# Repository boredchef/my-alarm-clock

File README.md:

# my alarm clock 
this is an alarm clock using a pcb with an esp32, buzzer and display. the alarm clock also has an enclosure designed in Onshape. to control the alarm clock there are 4 keyswitches and a rotary encoder knob. 

## challenges
for this project, the firmware needed a lot of different variables in order to function like the current time and the alarm time, the pins for the buttons and the different states for buttons, the overall clock and substate fields like setting hours/minutes while setting time. this project really helped me understand how to manage all these by defining functions for checking buttons or checking the time. 

## current features
* set time/alarm
* rotary encoder knob
* loud buzzer when alarm rings

## planned firmware features
* using display instead of serial monitor
* snooze alarm function

## BoM
| components | why/what | 
| ------ | ------ |
| esp32 c3 | microcontroller |
| MX-style keyboard switches | alarm controls | 
| 2.25 in TFT screen | display |
| 3.3v piezo buzzer | beep beep beep |
| 8 pin male header | for more pins |  
| jumper wire | connect display to headers |
| M3x8mm screws | connect case together | 
| rotary encoder knob | set hours/minutes | 

## more pictures
| alarm case | exploded view | back of pcb | front of pcb | pcb design | schematic | 
| ---- | ---- | ---- | ---- | ---- | ---- |
|  |  |  |  |  |  |

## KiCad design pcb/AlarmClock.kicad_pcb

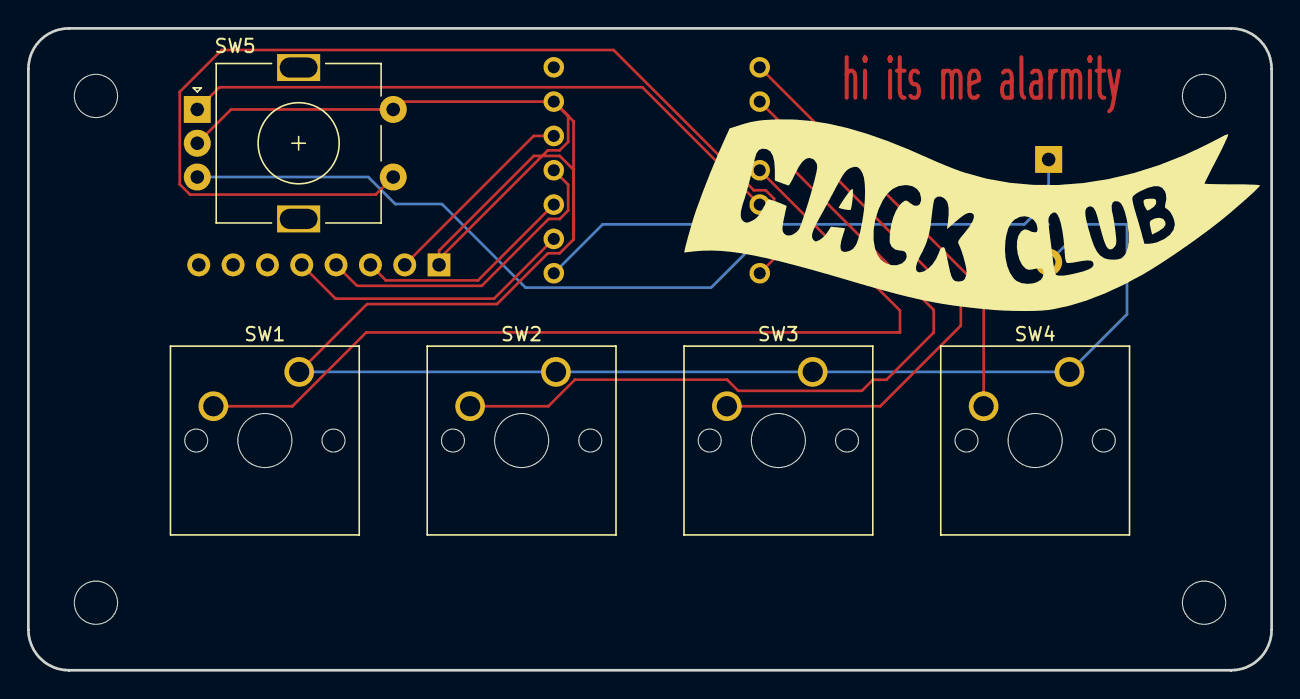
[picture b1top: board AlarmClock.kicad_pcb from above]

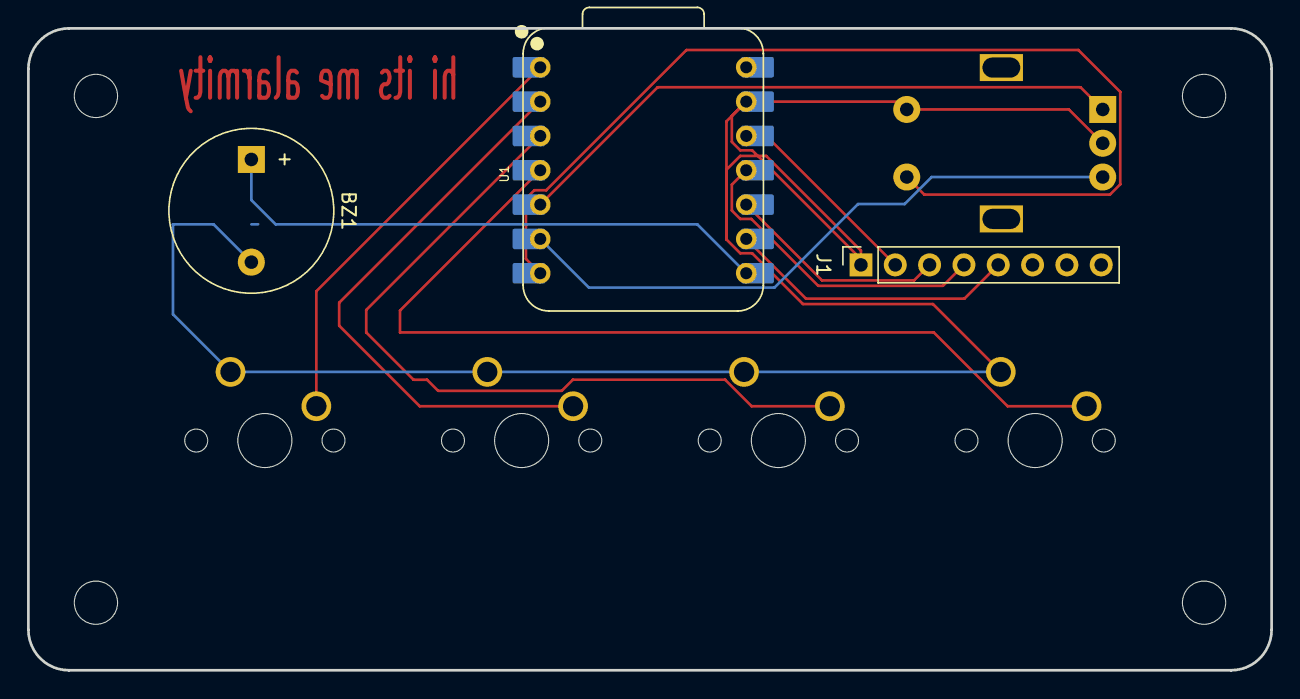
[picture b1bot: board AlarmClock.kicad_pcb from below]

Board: 2 copper layers, 92.0 x 47.5 mm, 12 parts (3 on the bottom side), 13 nets.

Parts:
BZ1: Buzzer; Buzzer_12x9.5RM7.6
H1, H2, H3, H4: MountingHole; MountingHole_3.2mm_M3
J1: Conn_01x08_Pin; PinSocket_1x08_P2.54mm_Vertical
SW1, SW2, SW3, SW4: SW_Push; SW_Cherry_MX_1.00u_PCB
SW5: RotaryEncoder_Switch; RotaryEncoder_Alps_EC11E-Switch_Vertical_H20mm
U1: XIAO-ESP32-C3-SMD; XIAO-ESP32-C3-DIP

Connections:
+3.3V: J1.2, U1.12 (3V3_OUT)
/A: SW5.A, U1.5 (D4)
/B: SW5.B, U1.6 (D5)
/RST: J1.5, U1.9 (D8)
/SCL: J1.3, U1.10 (D9/BOOT)
/SDA: J1.4, U1.11 (D10)
/SW: SW5.S1, U1.7 (D6)
GND: BZ1.2 (-), J1.1, SW1.1, SW2.1, SW3.1, SW4.1, SW5.C, SW5.S2, U1.13 (GND)
unnamed: BZ1.1 (+), U1.8 (D7)
unnamed: SW4.2, U1.1 (D0)
unnamed: SW3.2, U1.2 (D1)
unnamed: SW2.2, U1.3 (D2)
unnamed: SW1.2, U1.4 (D3)
